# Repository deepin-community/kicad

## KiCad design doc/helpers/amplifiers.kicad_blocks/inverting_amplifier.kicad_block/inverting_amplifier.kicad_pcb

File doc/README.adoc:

KiCad Documentation
===================

This repository contains the official link:https://www.kicad.org/[KiCad] documentation.

== Contributing

To help the development of the documentation, add issues to the
link:https://gitlab.com/kicad/services/kicad-doc/issues[issues page].

To help in translating the documentation visit the link:translation_instructions.adoc[]. +

To contribute code to the repository,
link:https://gitlab.com/kicad/services/kicad-doc/-/forks/new[fork the project],
commit changes to a branch on your fork, and
link:https://gitlab.com/kicad/services/kicad-doc/-/merge_requests[submit a merge request]. +
Submit your merge requests to the nightly docs branch `master`. If applicable,
your changes will also be applied to the stable branch after merging.

== Dependencies

* https://asciidoctor.org/[Asciidoctor] >= 2.0 is both the language of the
documentation and the tool used to generate the HTML outputs.

* https://github.com/Mogztter/asciidoctor-web-pdf[asciidoctor-web-pdf] is used to generate the
  PDF outputs.

* https://www.po4a.org/[po4a] v0.44 < version < v0.55 is used to translate the English
AsciiDoc documentation to other languages before the last compilation steps.
* CMake >= 3.0
* gettext >= 0.18

=== Debian / Ubuntu

To install the dependencies on Debian / Ubuntu run the following (requires
about 1.5GiB of space):

----

sudo apt-get install cmake ruby npm ninja-build fontconfig \
fonts-freefont-ttf fonts-wqy-microhei fonts-vlgothic gettext \
git make po4a source-highlight libunicode-linebreak-perl

sudo gem install asciidoctor

sudo npm i -g @asciidoctor/core asciidoctor-pdf --unsafe-perm

----

=== Fedora

To install the dependencies to build the documentation on Fedora, run the following:

   sudo dnf install -y cmake fontconfig po4a rubygem-asciidoctor npm git wqy-microhei-fonts
   sudo npm install -g puppeteer --unsafe-perm=true
   sudo npm install -g @asciidoctor/core asciidoctor-web-pdf --unsafe-perm=true

=== Arch/Manjaro Linux

To install the dependencies on Arch/Manjaro run the following:

    sudo pacman -S asciidoctor fontconfig po4a cmake gettext \
        perl-unicode-linebreak source-highlight ttf-freefont wqy-microhei

    yay -S asciidoctor-web-pdf ttf-vlgothic

== Building the docs

=== MacOS / Linux

    cd kicad-doc
    mkdir build
    cd build
    cmake ..
    make

or: Use ninja for accelerated compilation (Note: ninja needs to be installed)

    cd kicad-doc
    mkdir build
    cd build
    cmake -G Ninja ..
    ninja

=== Docker
https://gitlab.com/kicad/kicad-ci/doc_containers contains the base docker image with the tools preinstalled
to build the docs, if there is a need to update the base image, it must be done in that repo.

This repo contains its own Dockerfile intended to base on the build tools docker image and generate an empty
"archive" docker with just the generated files

=== CMake Build Options

==== BUILD_FORMATS

By default **BUILD_FORMATS** is set to `"html;pdf"` to enable building all supported
document formats.

It's possible to set **BUILD_FORMATS** in order to build only a subset of formats,
e.g. `-DBUILD_FORMATS=html`

When only one build format is enabled the package name is transformed to include
the format.

==== LANGUAGES

By default CMake will configure to build all languages available for each document.

You can build just one or some of the languages by using the **LANGUAGES** option
when configuring a build with CMake, e.g. `-DLANGUAGES="it;en;de"`, etc.

Currently, the available languages are : `ca`, `de`, `en`, `es`, `fr`, `id`,
`it`, `ja`, `pl`, `ru`  and `zh`, however, any language code can be selected.
Only translated documents will be built, so for some languages there may only
be a partial documentation output.

==== DOC_VERSION and DOC_COMMIT

These variables are used to set the version information printed in the
documentation. By default, these are set to reasonable values, so anyone
building the docs does not necessarily need to set these variables.

* `DOC_VERSION`: The current KiCad application version described by the docs
being built, in `major.minor.patch` format. If not specified, the value set in
this repository is used (see `CMakeModules/VersionInfo.cmake`).
* `DOC_COMMIT`: This is intended to be set to the current documentation commit
hash (i.e. the most recent commit hash in this repo). This value is printed
verbatim in the docs. If not specified, it is defaulted to the value of
`DOC_VERSION`, so the `major.minor.patch` version is printed instead of the
documentation commit hash.

Note that the defaults are fine for local development where you don't care
about the documentation containing accurate version numbers, commit hashes,
etc. The defaults are also probably fine for downstream packaging usecases.

==== PDF_GENERATOR

By default CMake will use `asciidoctor-web-pdf` for building PDFs. This is the
only supported PDF generator.

== Packaging the docs

The docs use CMake as mentioned earlier, so to install it as a packager use the
normal CMake way, for example:

    mkdir build; cd build
    cmake -DCMAKE_INSTALL_PREFIX=/usr ..
    make install

And if on OS X you might want something like:

    mkdir build; cd build
    cmake -DCMAKE_INSTALL_PREFIX="/Library/Application Support/kicad" ..
    make install

== Translating the docs

See the link:translating/translation_instructions.adoc[translation instructions].

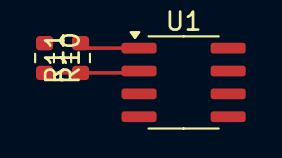
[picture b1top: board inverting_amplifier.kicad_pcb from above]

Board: 2 copper layers, 3 parts (0 on the bottom side), 2 nets.

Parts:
R10, R11: R; R_0603_1608Metric
U1: TL072; SOIC-8_3.9x4.9mm_P1.27mm

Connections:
/vout: R11.2, U1.1
unnamed: R10.2, R11.1, U1.2 (-)

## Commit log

2025-02-19 feat: update kicad to 8.0.8+dfsg-1~bpo12+1
2025-02-21 feat: update kicad to 8.0.8+dfsg-1
2025-03-26 feat: update kicad to 9.0.0+dfsg-1
2025-05-24 feat: update kicad to 9.0.2+dfsg-1
2026-04-14 feat: update kicad to 10.0.0+dfsg-1
